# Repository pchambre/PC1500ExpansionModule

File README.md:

# PC1500 Expansion Module (PSoC 5)

A PSoC 5-based hardware expansion board for the Sharp PC-1500/PC-2 pocket
computer, adding SD-card storage to PC-1500 BASIC via a set of new
`SD`-prefixed keywords (`SDLOAD`, `SDSAVE`, `SDLS`, `SDFMT`, ...).

The board plugs into the PC-1500's expansion port the same way a Sharp
CE-150/153/158 peripheral would, but unlike those (and unlike a real memory
module), the PSoC side has **no bus-request (BRQ) line** — it can't halt the
LH5801 CPU and take over the bus directly. Instead, the two sides
communicate through a shared 2KB RAM window mapped into the PC-1500's
address space: the CPU writes a command byte to a fixed "instruction"
address, the PSoC (polling that address in its own main loop) picks it up,
does the work, and writes its response into the same shared window. See
`PC_EXP.h` for the full wire protocol (command/status codes, buffer
layout).

## Companion emulator

[`pc1500emu`](https://github.com/pchambre/pc1500emu) is a from-scratch
PC-1500/LH5801 emulator with a matching `ExpansionMock` that implements this
same protocol against a real host directory — most of this board's firmware
and expansion-ROM development happens against the emulator (fast, no
hardware round-trip needed) and is only periodically verified against the
real PSoC board.

## Layout

This repo is a PSoC Creator workspace (`PC1500-PSOC5.cywrk`) containing
several `.cydsn` design variants, built up over the course of development.
**`Design01_NonDMA_8K_PV_Swap.cydsn` is the current, active design** — the
others (`Design01.cydsn`, `Design01_NonDMA.cydsn`,
`Design01_NonDMA_8KAddress_Space*.cydsn`, `Design01_NonDMA_8K_Swap2ndPage.cydsn`,
`Design02.cydsn`) are earlier iterations kept for reference, not maintained.

Inside the active design:

- `TopDesign/` — the PSoC 5 schematic (open with PSoC Creator to edit).
- `main.c` / `PC_EXP.h` — the PSoC-side firmware: the command processor
  (`DoCommand()`) that implements the shared-window wire protocol, backed
  by SEGGER emFile for the actual SD card filesystem calls.
- `rom/` — the PC-1500 expansion ROM, hand-written LH5801 assembly
  (`rom.asm`) that installs the new BASIC keywords. Assembled with
  [`sdaslh5801`](https://github.com/pchambre/sdcc-pc1500) via `build.ps1`,
  producing `rom_image.h` (baked into the PSoC firmware image so the module
  presents this ROM to the PC-1500 at boot) and a standalone `rom_8800.bin`
  (loadable directly into `pc1500emu` for fast iteration without a full
  PSoC Creator rebuild). See `rom/tests/` for a couple of small standalone
  test keywords used while reverse-engineering the PC-1500's own keyword
  dispatch mechanism.
- `SDCard/` — the emFile SD-card component wrapper.

Everything under `Generated_Source/`, `CortexM3/`, `codegentemp/`, and
`Export/` in each `.cydsn` folder is regenerated by PSoC Creator on build
and isn't tracked (see `.gitignore`) — open the workspace in PSoC Creator
and build to recreate it.

- `RP2350/` — an in-progress exploration of rearchitecting this board
  around the RP2350 (Pico 2 W) instead of PSoC 5 + ESP32-S3. Not yet the
  active design — see `RP2350/README.md` for the rationale and current
  state.

## Commands (implemented in `rom/rom.asm`)

- **`SDLS`** — browse the SD card's listing (current directory only, not
  recursive). Subdirectories are listed alongside files, with `<DIR>`
  (right-justified) in place of a size.
- **`SDFMT`** — format the SD card (`Y`/`N` confirmation).
- **`SDLOAD`** — load a BASIC program or binary data:
  - `SDLOAD` — browse, `L` selects and loads, `Enter` ignored, `CL`/`BREAK` abort.
  - `SDLOAD "<filename>"` — direct load, no browser.
  - `SDLOAD M` — browse, `L` loads the selected file as binary to its
    header's target address.
  - `SDLOAD M "<filename>"` — direct binary load to the file's header
    address; also `CALL`s an address embedded in the file, if present.
    On the internal card, a banked C program's file (`build-lh5801.sh
    --banks=card`) loads each of its banks too, then puts back the bank
    that was in before the `CALL`. Its header is `FFH 'B'`, the CALL
    address, a count, then per segment its bank (`FFH`: no switch),
    address and length.
  - `SDLOAD M "<filename>",<address>` — direct binary load, relocated to
    `<address>` (decimal or `&`-prefixed hex); never calls the embedded
    address.
  - A missing file raises a genuine BASIC `ERROR 40`.
- **`SDSAVE`** — save a BASIC program or binary data:
  - `SDSAVE "<filename>"[,-Y]` — saves the current BASIC program.
  - `SDSAVE M "<filename>",<start>,<end>[,<call>][,-Y]` — saves the
    inclusive RAM range `[start,end]` as binary, with an optional embedded
    call address for a later `SDLOAD M` to invoke automatically.
  - Both forms prompt to confirm before overwriting an existing file
    (`-Y` skips the prompt); missing/malformed required arguments raise
    `ERROR 1`.

- **`SDCD "<path>"`** — change the current directory. Every other SD
  command that takes a name (`SDLOAD`, `SDSAVE`, `SDLS`, `SDRM`, `SDCP`,
  `SDMV`, ...) resolves a plain filename relative to wherever this last
  left it. `"."`/`".."` and multi-component relative paths work; a
  nonexistent directory silently aborts (no error code raised for this
  specific case yet).
- **`SDMKDIR "<path>"`** — create a directory.
- **`SDRMDIR "<path>"`** — remove an *empty* directory (matches emFile's
  own `FS_RmDir`, which fails outright on a non-empty one rather than
  deleting its contents).
- **`SDPWD`** — print the current directory (`/` at the SD root, before
  any `SDCD`).
- **`SDRM "<path>"[,-Y]`** — delete a single file (never a directory —
  `SDRMDIR` is the only sanctioned way to remove one). Confirms first
  (`DELETE FILE? Y/N`, explicit `Y` proceeds, anything else including
  `BREAK` aborts) unless `-Y` is given. A missing argument raises
  `ERROR 1`; the file not existing (or being a directory) raises
  `ERROR 40`.
- **`SDCP "<src>","<dest>"`** — copy a file. `SDMV "<src>","<dest>"`
  — move (rename) a file. If `<dest>` resolves to an *existing directory*,
  the file lands inside it under its own basename, matching Unix `cp`/
  `mv`'s own "copy/move INTO a directory" behavior; otherwise `<dest>` is
  the exact target name. An existing destination is confirmed first
  (`FILE EXISTS. OVERWRITE Y/N`) unless `-Y` is given, matching `SDSAVE`/
  `SDRM`'s own convention. A missing argument raises `ERROR 1`; the source
  not existing (or any other copy/move failure) raises `ERROR 40`.
- **`SDDF`** — print free/total SD space (`<free>F / <total>T`).

- **`SDOPEN`/`SDCLOSE`/`SDINPUT#`/`SDPRINT#`/`SDSKIP#`** — up to 16
  variable-oriented SD files open at once, numbered 1-16 (a simplified,
  Apple-BASIC-style analogue of the CE-150's own `PRINT#`/`INPUT#`, which
  operate directly on named variables rather than file handles or byte
  offsets):
  - `SDOPEN "<filename>" AS <n>` — opens an existing file on channel
    `<n>`, read-only. A missing file is `ERROR 40`, and writes to the
    channel are `ERROR 40` too. `FOR R` (`SDOPEN "<filename>" FOR R AS <n>`)
    says the same explicitly.
  - `SDOPEN "<filename>" FOR W AS <n>` — opens it for reading and writing.
    The file is created if it doesn't exist; an existing file keeps its
    contents. A name that isn't a quoted literal takes the comma form:
    `SDOPEN F$ FOR W,<n>`.
  - Reusing an already-open channel number closes its previous file
    first. Open channels survive the dongle's POWMAN sleep. Bare `SDOPEN`
    (no arguments) browses currently open channels and their numbers
    (`Enter`/`CL`/`BREAK` all exit).
  - `SDCLOSE <n>` — closes channel `<n>`. `SDCLOSE ALL` closes every open
    channel.
  - `SDPRINT#<n>,<var>[,<var>...]` — appends one value per listed variable
    to the end of channel `<n>`'s file, always at the end regardless of
    the channel's own read position.
  - `SDINPUT#<n>,<var>[,<var>...]` — reads one value per listed variable
    from channel `<n>`'s own persistent read position, advancing past
    each one read. If the channel runs out, every remaining requested
    variable is set to `0` (numeric) or blank (string) rather than
    raising an error.
  - `SDSKIP#<n>,<count>` — skips forward `<count>` values in channel
    `<n>`'s own read position without reading them. All-or-nothing: if
    the channel runs out partway through, the read position is left
    completely unchanged and a genuine `ERROR 40` is raised. The comma
    between `<n>` and `<count>` is required — BASIC's own line editor
    does not reliably preserve a bare space between two digit runs
    outside a quoted string, confirmed live (`SDSKIP#1 2` silently lands
    in the input buffer as `#12`).
  - Only simple (non-array) numeric and string variables are supported —
    no arrays, no general expressions, matching the real `PRINT#`/
    `INPUT#`'s own variable-list-only grammar. Values are stored as
    self-describing chunks (`rom.asm` resolves each variable's own real
    RAM address via the base ROM's `D461H` "variable address search"
    system subroutine and copies its storage bytes directly — `main.c`/
    the emulator's `ExpansionMock` never see a variable name or value,
    only opaque chunk bytes): a numeric chunk is the variable's own
    8-byte packed-decimal float, copied verbatim; a string chunk is a
    1-byte length plus that many raw ASCII bytes (a simple string
    variable always holds ≤16 characters). Reading back a value chunk
    whose type doesn't match the target variable, or a string chunk
    longer than the target's own real capacity (only possible from a
    corrupted or hand-crafted file — a genuine `SDPRINT#` can never
    overflow what any variable could legitimately hold), raises `ERROR
    42`.
  - A missing/malformed argument to any of these five raises `ERROR 1`;
    referencing a channel number that isn't currently open raises `ERROR
    40` (the wire protocol can't distinguish "not open" from a genuine
    I/O failure, so neither can the ROM — both get the same code every
    other SD-operation-failure case already uses).
  - Values are always read/written/skipped sequentially, one whole value
    at a time. For raw bytes at a byte offset, use `SDREAD`/`SDWRITE`
    below on the same channel.
- **`SDREAD`/`SDWRITE`/`SDLOF`/`SDPOS`** (2026-10-29) — binary random
  access to an `SDOPEN` channel, moving raw bytes between RAM and the file.
  BASIC strings can't hold a 00H byte, so the bytes go to and from a RAM
  address and not a variable:
  - `SDREAD [#]<n>,<addr>,<len>[,<pos>]` — reads `<len>` bytes (0-65535)
    from channel `<n>`'s file into RAM at `<addr>`.
  - `SDWRITE [#]<n>,<addr>,<len>[,<pos>]` — writes `<len>` bytes from RAM
    at `<addr>` to the file.
  - **Position:** the transfer starts at byte `<pos>` if given. Otherwise
    it starts at the channel's own byte position, which is 0 at `SDOPEN`
    and separate from `SDINPUT#`'s value cursor. Afterwards the position
    sits just past the bytes moved.
  - **Writes** go over what's already there, or past the end, where the
    file grows. They are not appended like `SDPRINT#`'s.
  - **Reads** stop at the end of the file and leave the rest of the RAM
    alone. Reading at the end is not an error.
  - `SDLOF(<n>)` gives the file's size and `SDPOS(<n>)` its byte
    position. Both are functions, like `SDEOF`.
  - **Errors:** a channel that isn't open gives `ERROR 40`. A bad
    argument gives `ERROR 1`, and so does a RAM range that runs past
    FFFFH or into the module's own window at 8000H-87FFH.
  - **From machine code:** programs such as the Z-machine interpreter can
    send `SD_READ_BYTES`/`SD_WRITE_BYTES` directly and use the bytes in
    the window at 8000H. `RP2350/pc_exp.h` describes the sequence.

**Full path support**: every SD command's name argument (`SDLOAD`,
`SDSAVE`, `SDCD`, `SDMKDIR`, `SDRMDIR`, `SDRM`, and both `SDCP`/`SDMV`
arguments) accepts a plain filename, a relative path (`"SUB/FILE.BAS"`,
`"../FILE.BAS"`), or an absolute one from the SD root (`"/SUB/FILE.BAS"`,
or bare `"/"` for the root itself) — not just a bare filename in the
current directory. `/` is the one and only path separator — chosen
deliberately because it's an unshifted key on the PC-1500 keyboard, easy
to actually type. `main.c` converts to/from emFile's own native
`\`-separated, volume-prefixed paths at the boundary
(`PrepareFsName`/`ConvertSdPathToFsSeparators`), so nothing above that —
including the ROM side, which only ever sees/displays `/` — needs to know
emFile's own convention exists. A leading `/` with no volume prefix is
passed straight through to emFile, relying on its own path parser to
treat it as "from the SD root" (the same assumption `SDCD`'s own
`FS_ChDir` call already made — confirmed live for `SDCD` specifically,
not independently re-verified for every other command here).

`SDCD`/`SDMKDIR`/`SDRMDIR`/`SDRM`/`SDCP`/`SDMV` all require their
argument(s); missing one raises `ERROR 1`, matching `SDSAVE`'s own
convention.

**Uppercase 8.3 names**: this project's SD card uses SEGGER emFile's
No-Long-File-Name build (`emf32nosnlfn`, confirmed via this project's own
linker settings), so real on-disk names are genuine FAT 8.3 short names —
uppercase, `NAME.EXT` with an up-to-8-character name and an up-to-3-character
extension. Every SD command enforces this on its own argument(s):
lowercase letters are folded to uppercase automatically, and each
`/`-separated path segment that's too long, or has a second `.`, raises
`ERROR 1` (matching the existing unterminated/overlong-argument
convention) — except `SDLOAD`, which (per its own convention above)
silently aborts instead of raising an error for *any* malformed argument,
shape violations included. `.`/`..` segments are always exempt from the
shape check. A quoted argument itself is capped at 40 characters overall
— deliberately more than the 16-character width `SDLS`'s own listing
display column uses, since a path argument isn't shown in that fixed
column and can reasonably be longer.

The actual shape check + uppercase-folding runs on the PSoC/emulator side
(`EXP_COMMAND_VALIDATE_SD_NAME`, moved off `rom.asm` 2026-08-19) — `rom.asm`
itself only copies the raw typed name into the shared window and checks
for unterminated/overlong/empty before handing it off; the wire-level
`ERROR 1` behavior above is unchanged either way, since every call site
still just checks a Carry flag that means the same thing regardless of
which side actually did the validating.

**`+` stands in for `~`**: a card prepared on a normal PC (long filenames)
and then read by this project's NLFN firmware shows its auto-generated FAT
short names, which often contain a literal `~` (e.g. `MYAPPL~1.BAS`) — a
character the PC-1500 keyboard can't type. `+` is used as a typable
stand-in instead: `SDLS`/`SDPWD` show `+` wherever a real name has `~`,
and `SDLOAD`/`SDSAVE`/`SDCD`/`SDMKDIR`/`SDRMDIR` translate `+` back to `~`
before touching the real filesystem — including on create, so
`SDSAVE "APPL+1.BAS"` deliberately creates a file literally named
`APPL~1.BAS`. `+` (not `-`) was chosen specifically because it's illegal in
a real FAT 8.3 name, so the translation is unconditional and unambiguous in
both directions with zero risk of colliding with a genuinely `+`-named
file (impossible) — unlike `-`, which is a legal FAT 8.3 character.

BASIC-mode `SDLOAD`/`SDSAVE` target the program area's real, live start
address (tracked by BASIC itself in RAM at `7865H`/`7866H`, which shifts
depending on installed RAM — e.g. a CE-155 module moves it to `38C5H`),
not a hardcoded address, so they work correctly regardless of the PC-1500's
RAM configuration.

## Building

Requires PSoC Creator (this workspace was last built with PSoC Creator
4.x). Open `PC1500-PSOC5.cywrk`, select `Design01_NonDMA_8K_PV_Swap.cydsn`
as the active design, and Build. The ROM assembly step
(`rom/build.ps1`, needing `sdaslh5801` on `PATH`) must be run first if
`rom.asm` changed, so `rom_image.h` is up to date before the PSoC-side
build picks it up.

## License

Apache License 2.0 — see `LICENSE`.

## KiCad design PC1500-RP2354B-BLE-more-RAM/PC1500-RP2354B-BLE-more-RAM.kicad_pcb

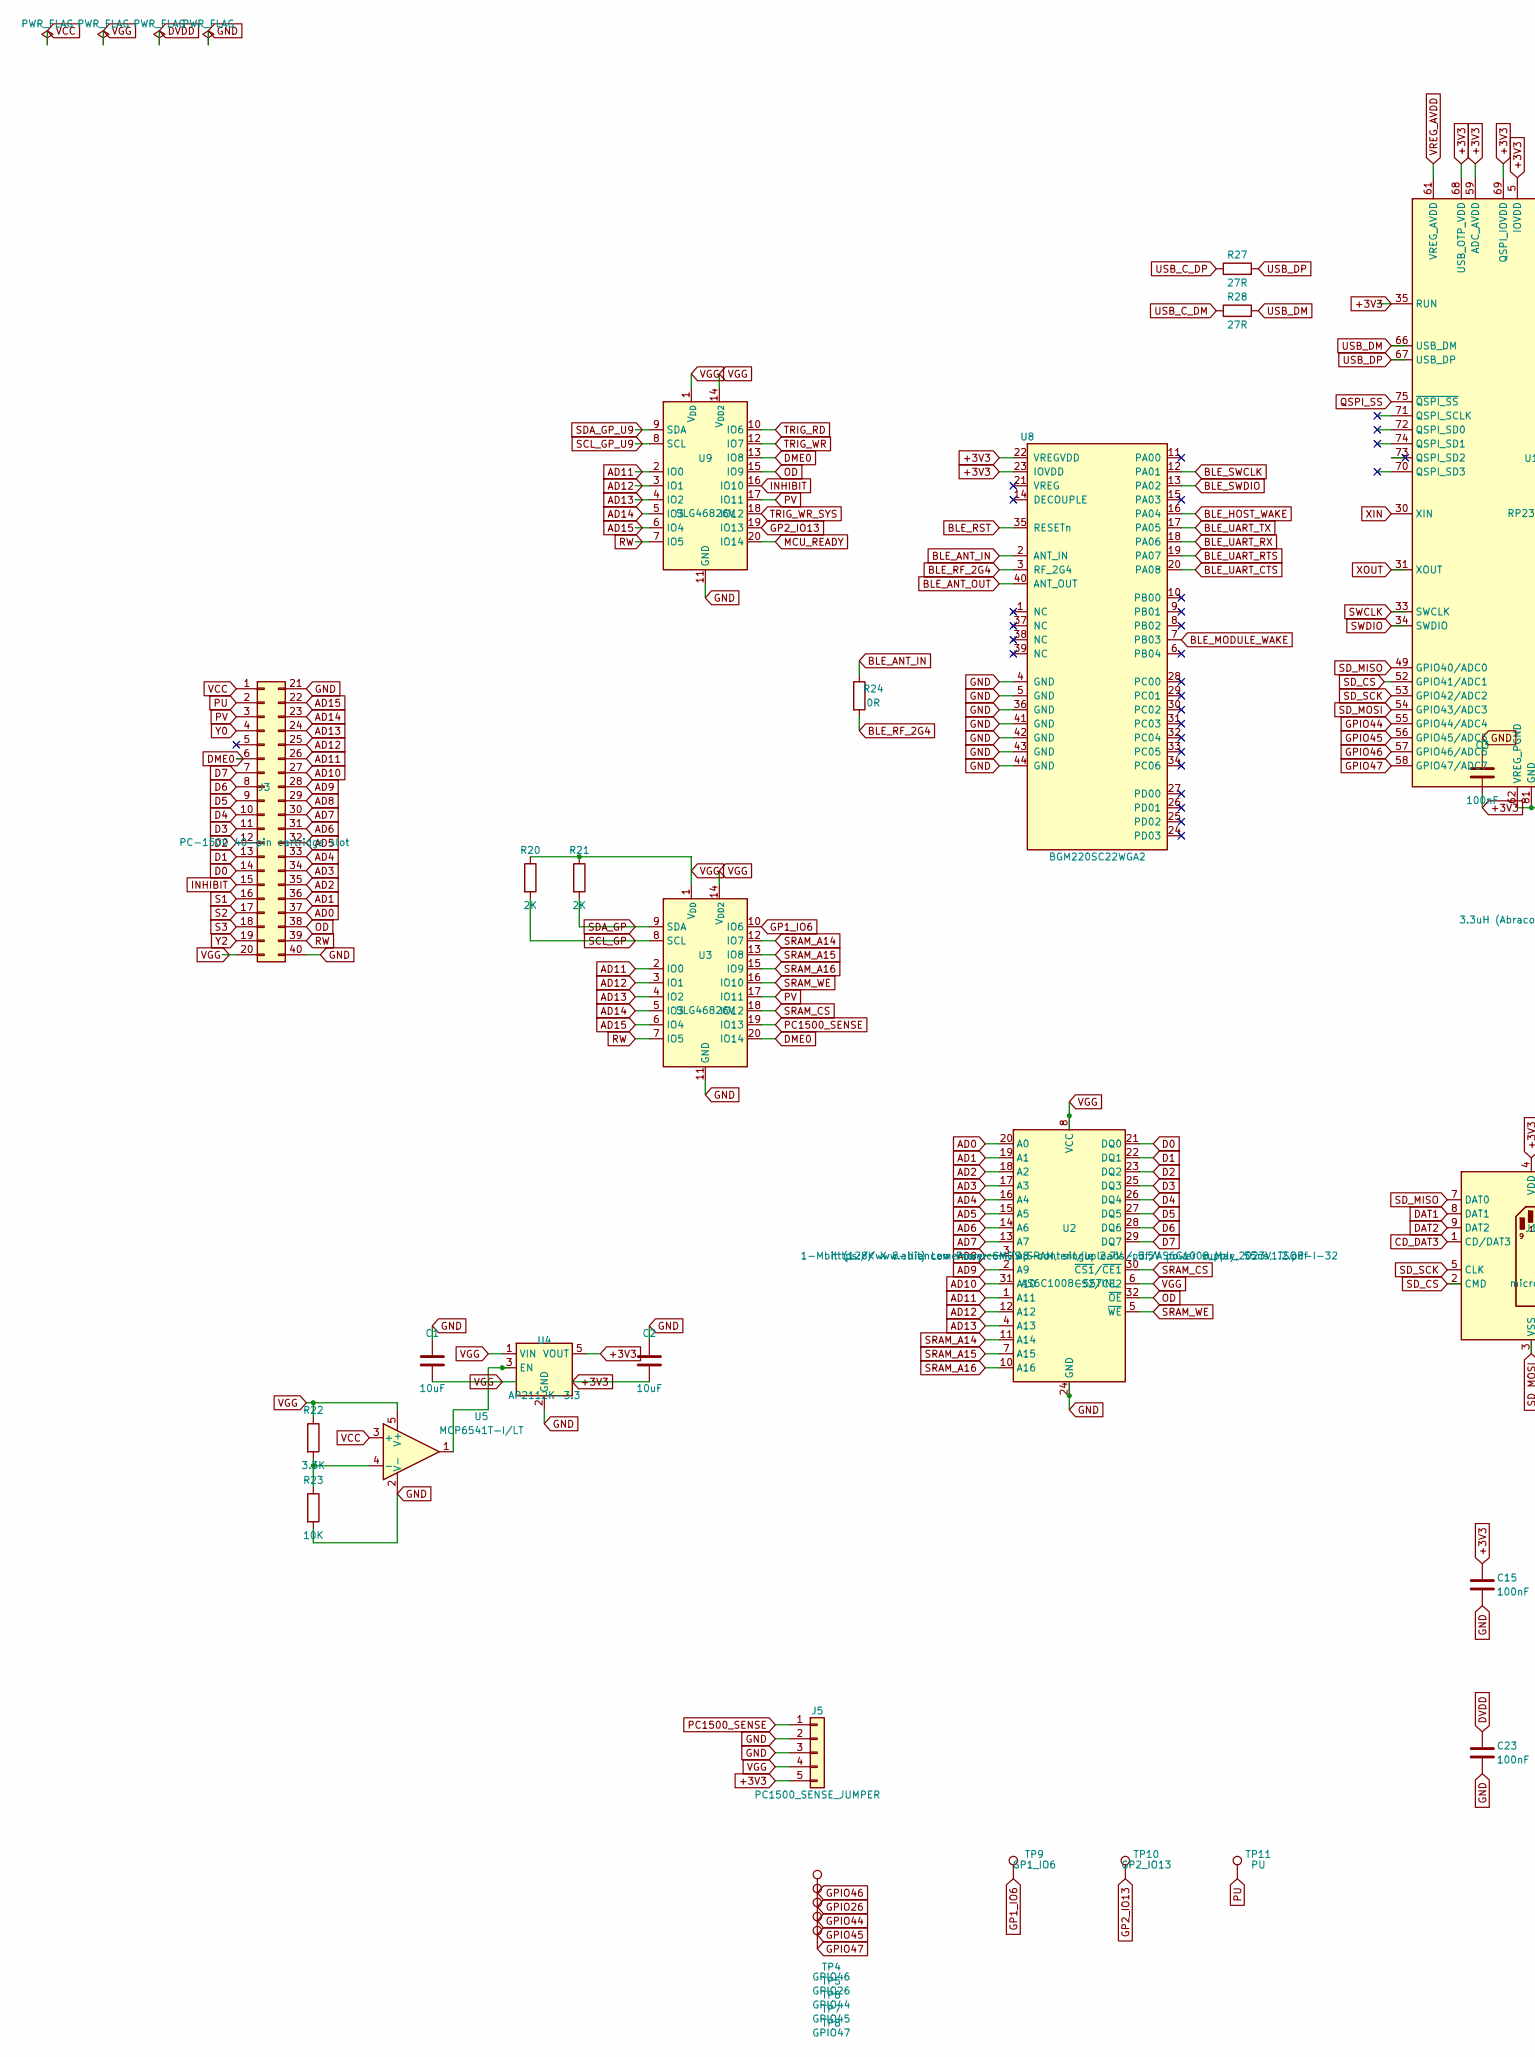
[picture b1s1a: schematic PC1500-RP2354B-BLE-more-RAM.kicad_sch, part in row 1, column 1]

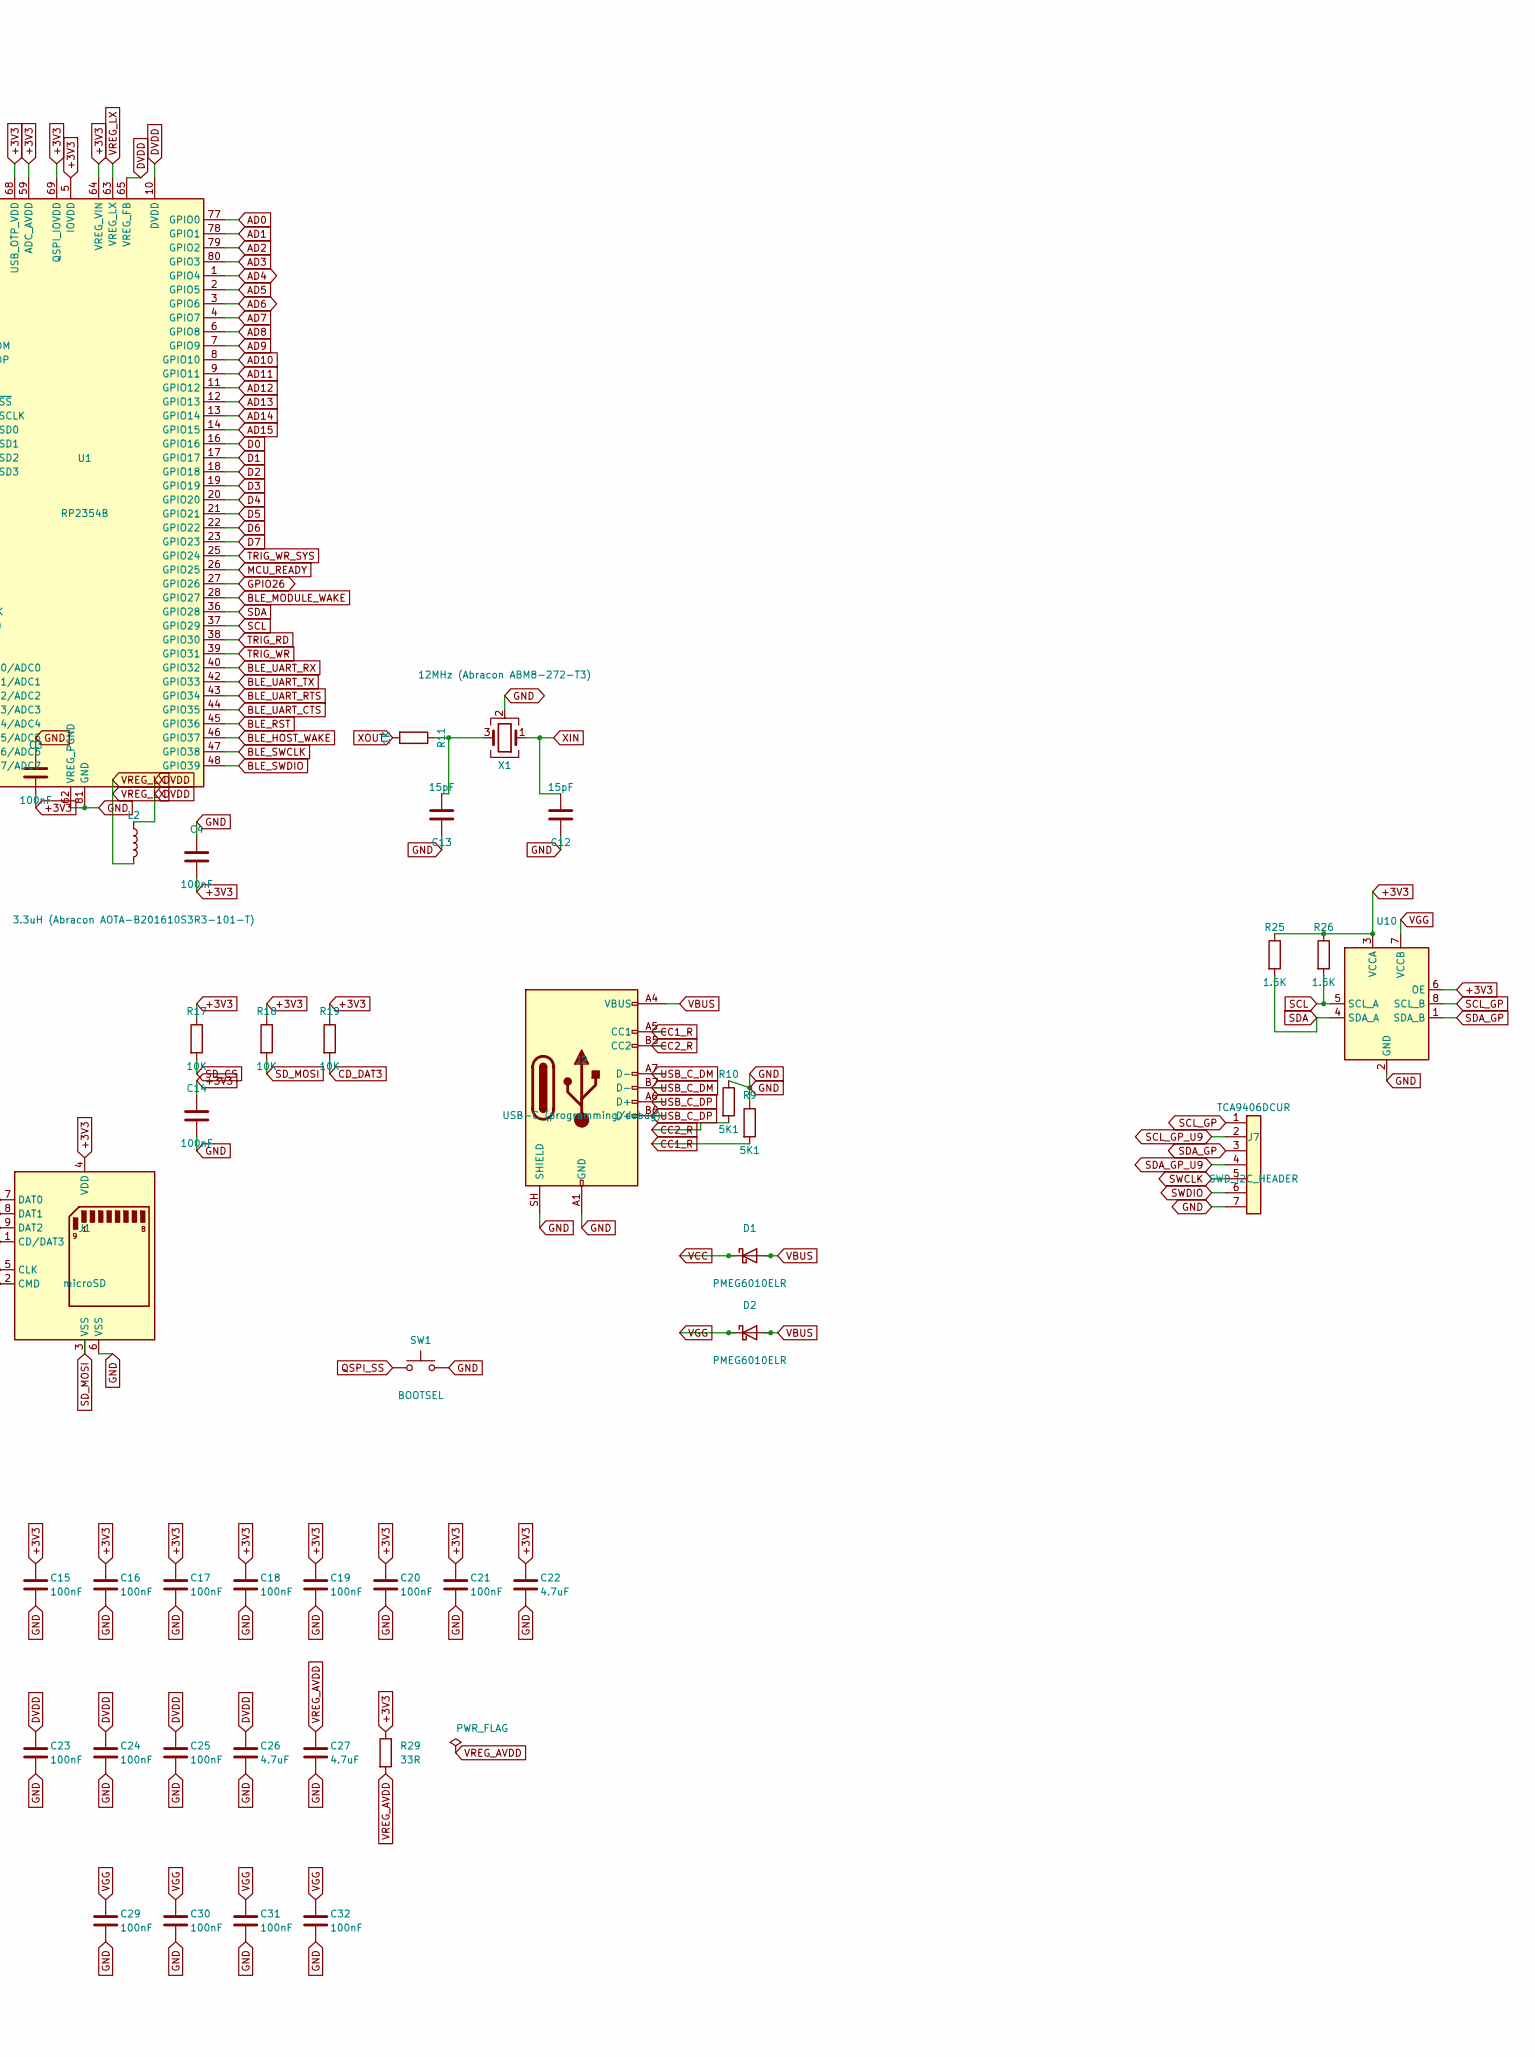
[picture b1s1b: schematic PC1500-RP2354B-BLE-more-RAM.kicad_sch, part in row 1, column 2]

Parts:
C1, C2: 10uF; C_0805_2012Metric
C3, C4, C14, C15, C16, C17, C18, C19, C20, C21, C23, C24, C25, C29, C30, C31, C32: 100nF; C_0402_1005Metric
C12, C13: 15pF; C_0603_1608Metric
C22, C26, C27: 4.7uF; C_0402_1005Metric
D1, D2: PMEG6010ELR; D_SOD-123F
FLG1, FLG2, FLG3, FLG4, FLG5: PWR_FLAG
J1: microSD; microSD_HC_Molex_104031-0811
J2: USB-C (programming/debug); USB_C_Receptacle_HRO_TYPE-C-31-M-12
J3: PC-1500 40-pin cartridge slot; SHARP-PC-CARTRIDGE
J5: PC1500_SENSE_JUMPER; PinHeader_1x05_P2.54mm_Vertical
J7: SWD_I2C_HEADER; PinHeader_1x07_P2.54mm_Vertical
L2: 3.3uH (Abracon AOTA-B201610S3R3-101-T); L_Abracon_AOTA-B201610; LCSC C42411119
R9, R10: 5K1; R_0201_0603Metric
R11: 1K; R_0201_0603Metric
R17, R18, R19, R23: 10K; R_0201_0603Metric
R20, R21: 2K; R_0201_0603Metric
R22: 3.3K; R_0201_0603Metric
R24: 0R; R_0402_1005Metric
R25, R26: 1.5K; R_0201_0603Metric
R27, R28: 27R; R_0402_1005Metric
R29: 33R; R_0402_1005Metric
SW1: BOOTSEL; SW_SPST_TL3342
TP4: GPIO46; TestPoint_Pad_1.0x1.0mm
TP5: GPIO26; TestPoint_Pad_1.0x1.0mm
TP6: GPIO44; TestPoint_Pad_1.0x1.0mm
TP7: GPIO45; TestPoint_Pad_1.0x1.0mm
TP8: GPIO47; TestPoint_Pad_1.0x1.0mm
TP9: GP1_IO6; TestPoint_Pad_1.0x1.0mm
TP10: GP2_IO13; TestPoint_Pad_1.0x1.0mm
TP11: PU; TestPoint_Pad_1.0x1.0mm
U1: RP2354B; QFN-80-1EP_10x10mm_P0.4mm_EP3.4x3.4mm
U2: AS6C1008-55TINL; TSOP-I-32_18.4x8mm_P0.5mm
U3, U9: SLG46826V; Renesas_UQFN-20_2x3mm_P0.4mm_LayoutBorder4x6y
U4: AP2112K-3.3; SOT-23-5
U5: MCP6541T-I/LT; SOT-23-5
U8: BGM220SC22WGA2; Silabs_BGM220S
U10: TCA9406DCUR; VSSOP-8_2.3x2mm_P0.5mm
X1: 12MHz (Abracon ABM8-272-T3); Crystal_SMD_3225-4Pin_3.2x2.5mm

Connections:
+3V3: C2.2, C3.2, C4.2, C14.1, C15.1, C16.1, C17.1, C18.1, C19.1, C20.1, C21.1, C22.1, J1.4 (VDD), J5.5, R17.1, R18.1, R19.1, R25.1, R26.1, R29.1, U1.5 (IOVDD), U1.15 (IOVDD), U1.24 (IOVDD), U1.29 (IOVDD), U1.35 (RUN), U1.41 (IOVDD), U1.50 (IOVDD), U1.59 (ADC_AVDD), U1.60 (IOVDD), U1.64 (VREG_VIN), U1.68 (USB_OTP_VDD), U1.69 (QSPI_IOVDD), U1.76 (IOVDD), U4.5 (VOUT), U8.22 (VREGVDD), U8.23 (IOVDD), U10.3 (VCCA), U10.6 (OE)
AD0: J3.37, U1.77 (GPIO0), U2.20 (A0)
AD1: J3.36, U1.78 (GPIO1), U2.19 (A1)
AD2: J3.35, U1.79 (GPIO2), U2.18 (A2)
AD3: J3.34, U1.80 (GPIO3), U2.17 (A3)
AD4: J3.33, U1.1 (GPIO4), U2.16 (A4)
AD5: J3.32, U1.2 (GPIO5), U2.15 (A5)
AD6: J3.31, U1.3 (GPIO6), U2.14 (A6)
AD7: J3.30, U1.4 (GPIO7), U2.13 (A7)
AD8: J3.29, U1.6 (GPIO8), U2.3 (A8)
AD9: J3.28, U1.7 (GPIO9), U2.2 (A9)
AD10: J3.27, U1.8 (GPIO10), U2.31 (A10)
AD11: J3.26, U1.9 (GPIO11), U2.1 (A11), U3.2 (IO0), U9.2 (IO0)
AD12: J3.25, U1.11 (GPIO12), U2.12 (A12), U3.3 (IO1), U9.3 (IO1)
AD13: J3.24, U1.12 (GPIO13), U2.4 (A13), U3.4 (IO2), U9.4 (IO2)
AD14: J3.23, U1.13 (GPIO14), U3.5 (IO3), U9.5 (IO3)
AD15: J3.22, U1.14 (GPIO15), U3.6 (IO4), U9.6 (IO4)
BLE_ANT_IN: R24.1, U8.2 (ANT_IN)
BLE_ANT_OUT: U8.40 (ANT_OUT)
BLE_HOST_WAKE: U1.46 (GPIO37), U8.16 (PA04)
BLE_MODULE_WAKE: U1.28 (GPIO27), U8.7 (PB03)
BLE_RF_2G4: R24.2, U8.3 (RF_2G4)
BLE_RST: U1.45 (GPIO36), U8.35 (RESETn)
BLE_SWCLK: U1.47 (GPIO38), U8.12 (PA01)
BLE_SWDIO: U1.48 (GPIO39), U8.13 (PA02)
BLE_UART_CTS: U1.44 (GPIO35), U8.20 (PA08)
BLE_UART_RTS: U1.43 (GPIO34), U8.19 (PA07)
BLE_UART_RX: U1.40 (GPIO32), U8.18 (PA06)
BLE_UART_TX: U1.42 (GPIO33), U8.17 (PA05)
CC1_R: J2.A5 (CC1), R9.2
CC2_R: J2.B5 (CC2), R10.2
CD_DAT3: J1.1 (CD/DAT3), R19.2
D0: J3.14, U1.16 (GPIO16), U2.21 (DQ0)
D1: J3.13, U1.17 (GPIO17), U2.22 (DQ1)
D2: J3.12, U1.18 (GPIO18), U2.23 (DQ2)
D3: J3.11, U1.19 (GPIO19), U2.25 (DQ3)
D4: J3.10, U1.20 (GPIO20), U2.26 (DQ4)
D5: J3.9, U1.21 (GPIO21), U2.27 (DQ5)
D6: J3.8, U1.22 (GPIO22), U2.28 (DQ6)
D7: J3.7, U1.23 (GPIO23), U2.29 (DQ7)
DAT1: J1.8 (DAT1)
DAT2: J1.9 (DAT2)
DME0: J3.6, U3.20 (IO14), U9.13 (IO8)
DVDD: C23.1, C24.1, C25.1, C26.1, FLG3.1, L2.1, U1.10 (DVDD), U1.32 (DVDD), U1.51 (DVDD), U1.65 (VREG_FB)
GND: C1.1, C2.1, C3.1, C4.1, C12.1, C13.1, C14.2, C15.2, C16.2, C17.2, C18.2, C19.2, C20.2, C21.2, C22.2, C23.2, C24.2, C25.2, C26.2, C27.2, C29.2, C30.2, C31.2, C32.2, FLG4.1, J1.6 (VSS), J2.A1 (GND), J2.A12 (GND), J2.B1 (GND), J2.B12 (GND), J2.SH (SHIELD), J3.21, J3.40, J5.2, J5.3, J7.7, R9.1, R10.1, R23.2, SW1.2, U1.62 (VREG_PGND), U1.81 (GND), U2.24 (GND), U3.11 (GND), U4.2 (GND), U5.2 (V-), U8.4 (GND), U8.5 (GND), U8.36 (GND), U8.41 (GND), U8.42 (GND), U8.43 (GND), U8.44 (GND), U9.11 (GND), U10.2 (GND), X1.2 (G), X1.4 (G)
GP1_IO6: TP9.1 (1_1), U3.10 (IO6)
GP2_IO13: TP10.1 (1_1), U9.19 (IO13)
GPIO26: TP5.1 (1_1), U1.27 (GPIO26)
GPIO44: TP6.1 (1_1), U1.55 (GPIO44/ADC4)
GPIO45: TP7.1 (1_1), U1.56 (GPIO45/ADC5)
GPIO46: TP4.1 (1_1), U1.57 (GPIO46/ADC6)
GPIO47: TP8.1 (1_1), U1.58 (GPIO47/ADC7)
INHIBIT: J3.15, U9.16 (IO10)
MCU_READY: U1.26 (GPIO25), U9.20 (IO14)
unnamed: C13.2, R11.1, X1.3
unnamed: U4.3 (EN), U5.1
unnamed: R22.2, R23.1, U5.4 (-)
OD: J3.38, U2.32 (~OE), U9.15 (IO9)
PC1500_SENSE: J5.1, U3.19 (IO13)
PU: J3.2, TP11.1 (1_1)
PV: J3.3, U3.17 (IO11), U9.17 (IO11)
QSPI_SS: SW1.1, U1.75 (~QSPI_SS)
RW: J3.39, U3.7 (IO5), U9.7 (IO5)
S1: J3.16
S2: J3.17
S3: J3.18
SCL: R26.2, U1.37 (GPIO29), U10.5 (SCL_A)
SCL_GP: J7.1, R20.2, U3.8 (SCL), U10.8 (SCL_B)
SCL_GP_U9: J7.2, U9.8 (SCL)
SDA: R25.2, U1.36 (GPIO28), U10.4 (SDA_A)
SDA_GP: J7.3, R21.2, U3.9 (SDA), U10.1 (SDA_B)
SDA_GP_U9: J7.4, U9.9 (SDA)
SD_CS: J1.2 (CMD), R17.2, U1.52 (GPIO41/ADC1)
SD_MISO: J1.7 (DAT0), U1.49 (GPIO40/ADC0)
SD_MOSI: J1.3 (VSS), R18.2, U1.54 (GPIO43/ADC3)
SD_SCK: J1.5 (CLK), U1.53 (GPIO42/ADC2)
SRAM_A14: U2.11 (A14), U3.12 (IO7)
SRAM_A15: U2.7 (A15), U3.13 (IO8)
SRAM_A16: U2.10 (A16), U3.15 (IO9)
SRAM_CS: U2.30 (~CS1/~CE1), U3.18 (IO12)
SRAM_WE: U2.5 (~WE), U3.16 (IO10)
SWCLK: J7.5, U1.33 (SWCLK)
SWDIO: J7.6, U1.34 (SWDIO)
TRIG_RD: U1.38 (GPIO30), U9.10 (IO6)
TRIG_WR: U1.39 (GPIO31), U9.12 (IO7)
TRIG_WR_SYS: U1.25 (GPIO24), U9.18 (IO12)
USB_C_DM: J2.A7 (D-), J2.B7 (D-), R28.1
USB_C_DP: J2.A6 (D+), J2.B6 (D+), R27.1
USB_DM: R28.2, U1.66 (USB_DM)
USB_DP: R27.2, U1.67 (USB_DP)
VBUS: D1.2 (A), D2.2 (A), J2.A4 (VBUS), J2.A9 (VBUS), J2.B4 (VBUS), J2.B9 (VBUS)
VCC: D1.1 (K), FLG1.1, J3.1, U5.3 (+)
VGG: C1.2, C29.1, C30.1, C31.1, C32.1, D2.1 (K), FLG2.1, J3.20, J5.4, R20.1, R21.1, R22.1, U2.6 (CS2/CE2), U2.8 (VCC), U3.1 (V_{DD}), U3.14 (V_{DD2}), U4.1 (VIN), U5.5 (V+), U9.1 (V_{DD}), U9.14 (V_{DD2}), U10.7 (VCCB)
VREG_AVDD: C27.1, FLG5.1, R29.2, U1.61 (VREG_AVDD)
VREG_LX: L2.2, U1.63 (VREG_LX)
XIN: C12.2, U1.30 (XIN), X1.1
XOUT: R11.2, U1.31 (XOUT)
Y0: J3.4
Y2: J3.19

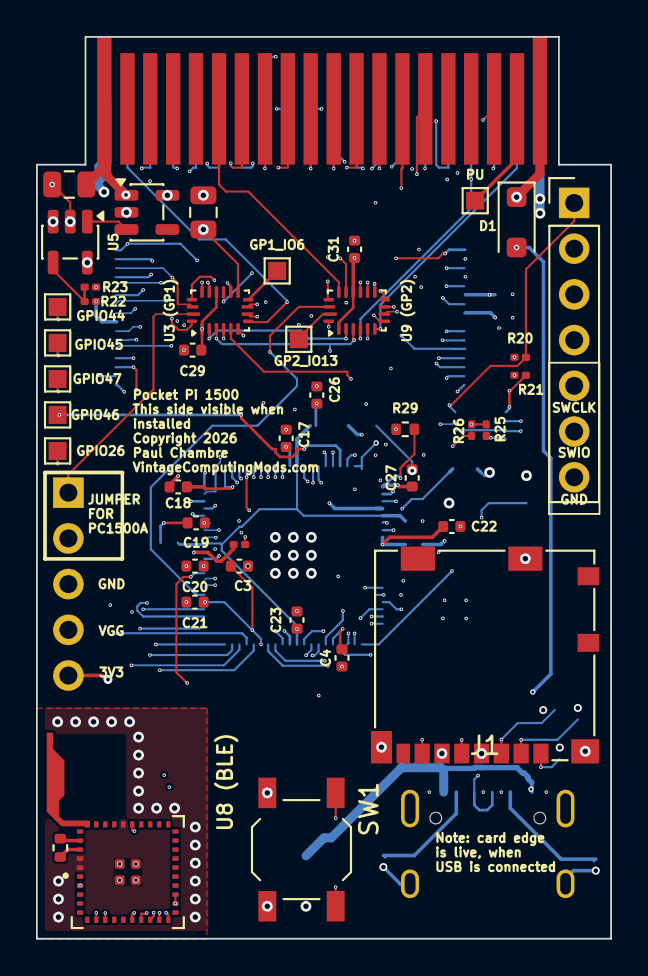
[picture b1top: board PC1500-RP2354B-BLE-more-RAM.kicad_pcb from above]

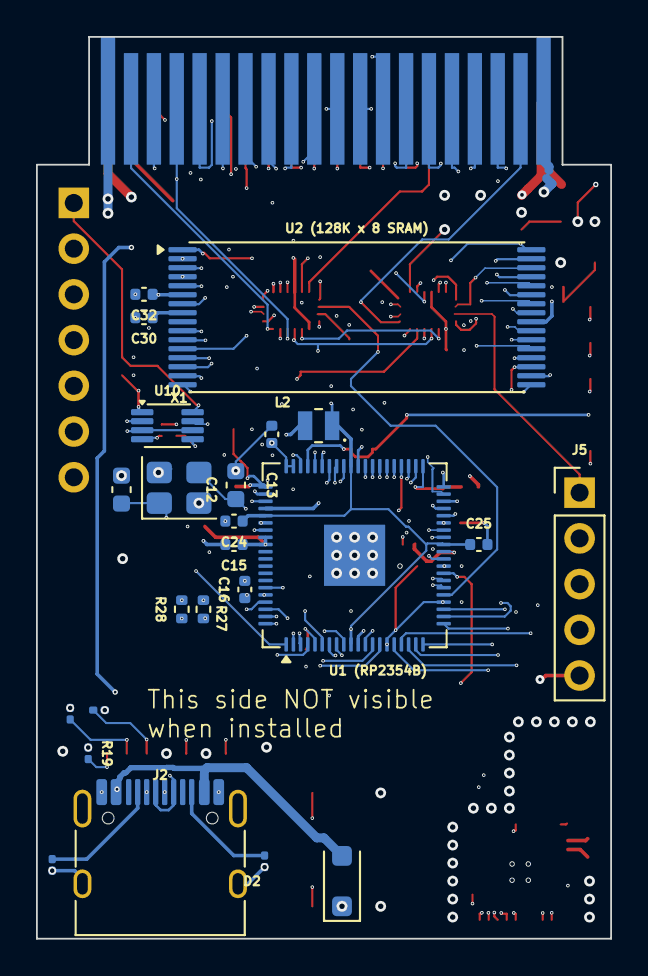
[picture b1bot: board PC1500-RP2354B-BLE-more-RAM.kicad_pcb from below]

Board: 8 copper layers, 31.9 x 50.1 mm, 66 parts (24 on the bottom side), 91 nets.

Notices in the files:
PC1500-ROM-Replacement-Board/PC1500-ROM-Replacement-Board.kicad_pcb:
Copyright 2026 Paul Chambre
parts and their libraries:
Pad pitch/order sourced from https://github.com/kaibader/Sharp-PC-Breakout-Boards/tree/main/Breakout-Cartridge (CC BY-SA 4.0, Kai C.
